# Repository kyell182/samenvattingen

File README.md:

# Samenvattingen ICT & Elektronica

Studiemateriaal uit mijn opleiding Elektronica-ICT aan VIVES: samenvattingen, cheatsheets, labo-verslagen en uitgewerkte opdrachten, geordend per jaar en per vak.

## Overzicht

### 1ste jaar

| Vak | Inhoud |
| :-- | :-- |
| [Digital technologie](1ste-jaar/digital%20technologie/) | Digitaal rekenen, logische poorten, tellers en flip-flops |
| [Electronica STEM](1ste-jaar/electronica%20stem/) | Weerstanden, dioden, versterkers en oscilloscoop |
| [Electronics](1ste-jaar/electronics/) | Theorie, LTspice-labo en examenvoorbereiding |
| [Introduction to gaming](1ste-jaar/introduction%20to%20gaming/) | Hardwareanalyse van de PlayStation 4 Pro |
| [Microsoft management](1ste-jaar/microsoft%20management/) | Netwerkbeheer met Windows Server 2022 |
| [PCB design](1ste-jaar/pcb%20design/) | Schema's en printplaten (LM555, IO-expander) |
| [Prototyping](1ste-jaar/prototyping/) | 3D-printen, lasersnijden en Arduino |
| [Web essentials](1ste-jaar/web%20essentials/) | HTML, CSS, Bootstrap, JavaScript en Web API's |

### 2de jaar

| Vak | Inhoud |
| :-- | :-- |
| [AI Fundamentals](2de-jaar/AI%20Fundamentals/) | Machine learning, neurale netwerken en zoekalgoritmen |
| [AI Programming](2de-jaar/AI%20Programming/) | Python, NumPy, pandas en PyTorch |
| [AI math](2de-jaar/ai%20math/) | Vectoren, matrices en de wiskunde achter AI |
| [Applied Math](2de-jaar/Applied%20Math/) | Lettervormen, vergelijkingen, afgeleiden en integralen |
| [Computer architectuur](2de-jaar/computer%20architectuur/) | Processoren, geheugen en prestatieverbetering |
| [Cybersecurity](2de-jaar/cybersecurity/) | Nmap, OSINT, Hashcat en picoCTF-challenges |
| [Databases](2de-jaar/Databases/) | Databankontwerp, SQL en security |
| [IoT devices](2de-jaar/IoT%20devices/) | I2C, SPI, WiFi en RTOS op microcontrollers |
| [Linux](2de-jaar/Linux/) | Systeembeheer, rechten, netwerk en containers |

### 3de jaar

Nog niet gestart.

## Structuur

```
samenvattingen/
  1ste-jaar/<vak>/     samenvattingen, cursusmateriaal, labo's en opdrachten
  2de-jaar/<vak>/
  3de-jaar/
  index.md             startpagina van de website
  _config.yml          Jekyll-instellingen
  .github/workflows/   automatische publicatie naar GitHub Pages
```

Elk vak heeft een `index.md` met een overzicht van de beschikbare bestanden. Samenvattingen zijn geschreven in markdown, bijbehorende bronbestanden zijn PDF, Word of Excel.

## Website lokaal bekijken

De repo wordt met Jekyll gepubliceerd op GitHub Pages. Om de site lokaal te testen heb je Ruby en Bundler nodig:

```bash
gem install jekyll bundler
jekyll serve
```

De site is daarna bereikbaar op `http://localhost:4000`.

## Gebruik

Het materiaal is bedoeld als persoonlijke studiehulp en kan fouten bevatten. Controleer belangrijke zaken altijd in de officiële cursus.

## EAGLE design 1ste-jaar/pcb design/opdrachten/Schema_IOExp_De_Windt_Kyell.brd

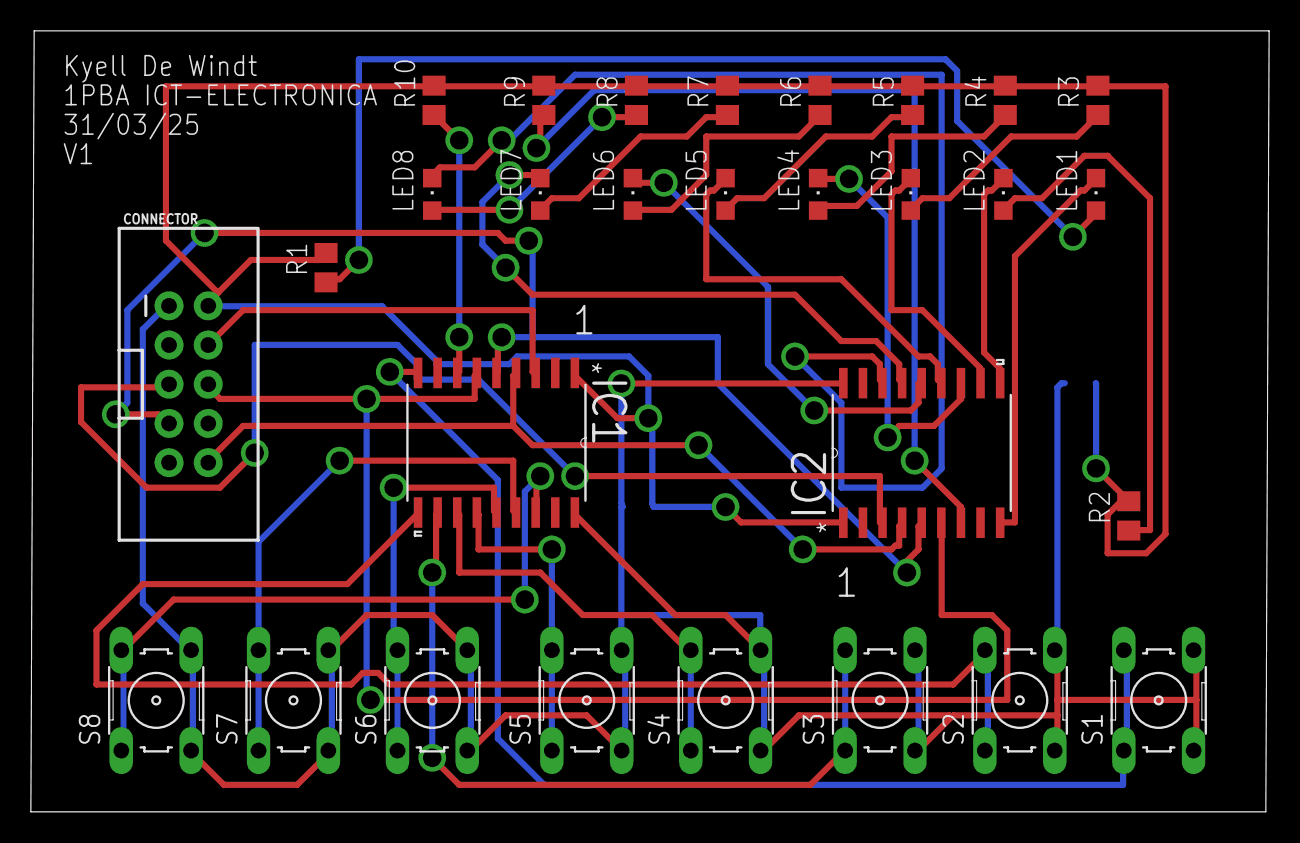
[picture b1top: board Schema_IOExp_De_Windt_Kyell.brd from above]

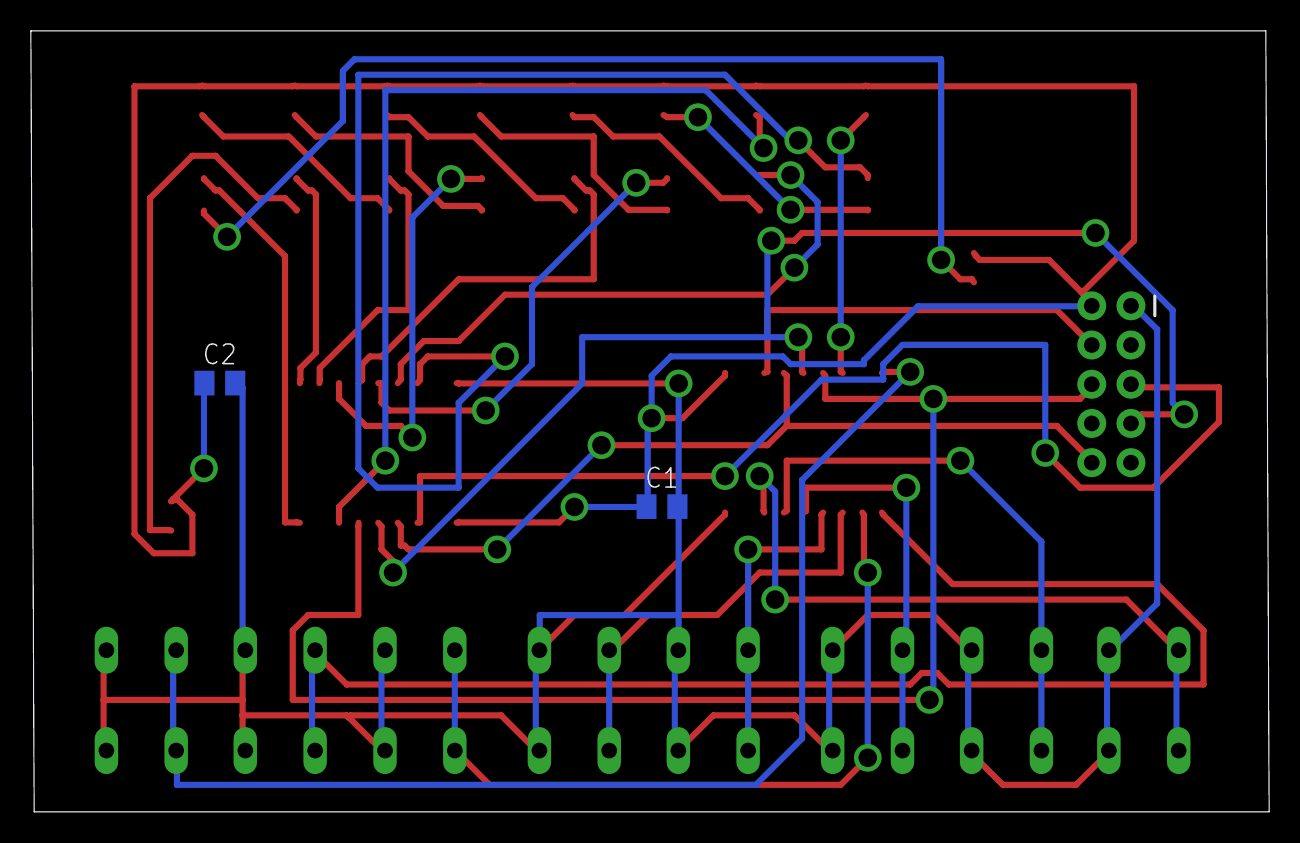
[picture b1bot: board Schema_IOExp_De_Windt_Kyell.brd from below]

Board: 2 copper layers, 80.2 x 50.6 mm, 31 parts (2 on the bottom side), 33 nets.

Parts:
C1, C2: 100nF; C0805K
CONNECTOR: SV1; 2X5-SHROUDED
IC1, IC2: MCP23S09-E/SO; SOIC127P1030X265-18N
LED1, LED2, LED3, LED4: groen; CHIPLED_0805
LED5, LED6: geel; CHIPLED_0805
LED7, LED8: rood; CHIPLED_0805
R1, R2: 10K; R0805
R3, R4, R5, R6, R7, R8: 100; R0805
R9, R10: 68; R0805
S1, S2, S3, S4, S5, S6, S7, S8: B3F-10XX

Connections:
CH1: CONNECTOR.4, IC1.3
CH2: CONNECTOR.5, IC2.3
DRUKKNOP1: IC1.9, S1.1, S1.2
DRUKKNOP2: IC1.10, S2.1, S2.2
DRUKKNOP3: IC1.11, S3.1, S3.2
DRUKKNOP4: IC1.12, S4.1, S4.2
DRUKKNOP5: IC1.13, S5.1, S5.2
DRUKKNOP6: IC1.14, S6.1, S6.2
DRUKKNOP7: IC1.15, S7.1, S7.2
DRUKKNOP8: IC1.16, S8.1, S8.2
GND: C1.2, C2.2, CONNECTOR.1, IC1.18, IC2.18, S1.3, S1.4, S2.3, S2.4, S3.3, S3.4, S4.3, S4.4, S5.3, S5.4, S6.3, S6.4, S7.3, S7.4, S8.3, S8.4
LED1: IC2.9, LED1.C
LED2: IC2.10, LED2.C
LED3: IC2.11, LED3.C
LED4: IC2.12, LED4.C
LED5: IC2.13, LED5.C
LED6: IC2.14, LED6.C
LED7: IC2.15, LED7.C
LED8: IC2.16, LED8.C
MISO: CONNECTOR.6, IC1.6, IC2.6
MOSI: CONNECTOR.7, IC1.5, IC2.5
unnamed: LED8.A, R8.1
unnamed: LED7.A, R7.1
unnamed: LED6.A, R6.1
unnamed: LED5.A, R5.1
unnamed: LED4.A, R4.1
unnamed: LED3.A, R3.1
unnamed: LED2.A, R2.1
unnamed: LED1.A, R1.1
unnamed: IC2.7, R9.1
unnamed: IC1.7, R10.1
SCK: CONNECTOR.10, IC1.4, IC2.4
VDD: C1.1, C2.1, CONNECTOR.2, IC1.1, IC2.1, R1.2, R2.2, R3.2, R4.2, R5.2, R6.2, R7.2, R8.2, R9.2, R10.2

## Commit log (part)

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2025-12-29 Fresh start - cleaned repository
2025-12-29 Remove nested submodules from tracking
2025-12-29 added readme quiz iot
2025-12-29 update iot readme
2025-12-29 Format answers as bullet points for clarity in IoT questions.
2025-12-29 Refactor IoT study guide: update structure and quiz questions for clarity and consistency
2025-12-30 Refactor code structure and remove redundant code blocks for improved readability and maintainability
2025-12-30 Fix formatting of question 3.1 for consistency in IoT devices README
2025-12-30 Improve formatting and clarity of polling, interrupt, and DMA sections in IoT devices README
2025-12-30 Fix bullet point formatting for clarity in advantages and disadvantages sections of IoT devices README
2025-12-30 Add chapters and assets for Databases course
    - Added Chapter 5: Calculated fields and functions (PDF)
    - Added Chapter 6: Joins (PDF)
    - Added Chapter 7: Subqueries (PDF)
    - Added Chapter 8: Write queries (PDF)
    - Added Chapter 9: Views, functions, and stored procedures (PDF)
    - Added various assets including images for data flow, Excel, CSV, and infographics
2025-12-30 Fix detail tag formatting to ensure proper rendering in Databases summary
2025-12-30 Refactor code structure for improved readability and maintainability
2025-12-30 Fix image file naming for XML and JSON file types for consistency
2025-12-30 Add additional file types and corresponding images to the Databases summary
2025-12-30 Improve formatting and clarity in DBMS section of Databases summary
2025-12-30 Fix formatting issue in RDBMS section for consistency
2025-12-30 Fix typos and improve clarity in database summary documentation
2025-12-30 Add new chapters on database design and SQL queries to the documentation
2025-12-30 Add ERD examples and symbols to the database summary documentation
2025-12-30 Add sample data insertion for 'leden' table in database documentation
2025-12-30 Remove unnecessary image for database creation example in documentation
2026-01-01 Add a newline before the chapter heading for better formatting
2026-01-01 Format SQL queries in code blocks for better readability
2026-01-01 Format SQL code in a code block for improved readability
2026-01-01 added ai fundamentals
2026-01-02 Format mathematical equations for improved clarity and consistency
2026-01-02 Add images for speed and acceleration calculations to enhance understanding
2026-01-02 Add images for speed and acceleration to enhance learning resources
2026-01-02 rrrr
2026-01-02 Fix calculation error in AI Fundamentals summary for clarity
2026-01-02 mind is exploding
2026-01-02 Enhance explanation of Perceptron as a linear classifier for clarity
2026-01-02 Add perceptron dataset image to AI Fundamentals summary
2026-01-02 Add introduction to Perceptron Learning Algorithm in AI Fundamentals summary
2026-01-02 Add techniques to improve convergence speed of Perceptron Learning Algorithm and include normalization image
2026-01-03 added ai math
2026-01-03 Add vector graphics for various mathematical concepts
    - Added 'nul vector grafisch.png' to represent the null vector visually.
    - Added 'nul vector.png' for a different representation of the null vector.
    - Introduced 'vecor in oorsprong grafisch.png' to illustrate the vector in its original form.
    - Included 'vector in de oorsprong .png' to depict the vector in its origin.
    - Added 'vector in de oorsprong .png' for additional visual representation of vectors in their origin.
2026-01-03 Fix notation for vector norm in AI math summary
2026-01-03 Fix formatting for unit vector notation in AI math summary
2026-01-03 Fix notation for vector addition in 3D representation
2026-01-03 Fix formatting issues in vector representation for clarity
2026-01-03 Fix formatting issues in 2D vector representation for consistency
2026-01-03 Add clarification on orthogonality of basis vectors in 2D representation
2026-01-03 Fix formatting issues in 2D basis vector representation for clarity
2026-01-03 Fix formatting issues in 2D basis vector representation for consistency
2026-01-03 Fix formatting issues in 3D basis vector representation for clarity
2026-01-03 Add clarification on scalar multiplication and distance between points in vector representation
2026-01-04 update linux folder with tagged pdfs and additional resources
2026-01-05 Add detailed descriptions for common Linux commands and enhance clarity
2026-01-05 Fix example of relative path in Linux guide for accuracy
2026-01-07 added computer architectuur
2026-01-08 Add 6502 microprocessor instruction set and reference questions
    - Introduced a comprehensive markdown document detailing the instruction set for the 6502 microprocessor, including various categories such as loading and storing registers, arithmetic operations, lo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
    - Added a reference document containing questions and answers related to computer architecture, covering topics from the history of computing to modern processor architectures and performance techniq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
2026-01-08 added h2
2026-01-08 fixed ascii garbage
2026-01-08 Add details on page directory and table entries for virtual memory explanation
2026-01-08 Update virtual memory explanation with additional details on page directory and table entries
2026-01-08 Fix indentation and formatting issues in virtual memory explanation
2026-01-09 h8 klaar
2026-01-09 h9 klaar
2026-01-15 Fix formatting issues in mathematical expressions and update flowchart structure for clarity
2026-01-15 Improve formatting and clarity of k-Nearest Neighbor algorithm section with additional details and mathematical expressions
2026-01-15 Update sigmoid function representation and clarify Hebb rule description
2026-01-17 Add comprehensive cheatsheets for Python libraries and AI programming concepts
    - Created a summary document for AI Programming covering key concepts and definitions.
    - Added cheatsheets for argparse, datetime, json, math, matplotlib, numpy, os, pandas, pytorch, queue, random, and requests libraries.
2026-01-17 Add alpha-beta pruning explanation and genetic algorithms overview
2026-01-17 Fix math formatting for alpha-beta pruning explanation
2026-01-18 Add advanced evolutionary approaches and swarm intelligence concepts
2026-01-18 Refine formatting of stop criteria for Ant Colony Optimization algorithm
2026-01-18 afgewerkte sammvating AI programming
2026-01-19 Update section title and clarify particle position update explanation in swarm intelligence
2026-01-19 Add section break before the ant optimization algorithm explanation
2026-01-19 Add explanation for the importance of fitness function in genetic algorithms
2026-01-19 Add explanation for chromosome encoding in genetic algorithms
2026-01-19 Update calculation for function f(e) to include additional path cost
2026-01-19 Refactor terminology section to improve clarity and formatting of graph-related terms
2026-01-19 Fix order of nodes in graph example for clarity
2026-01-19 Refactor tree terminology section for improved clarity and formatting
2026-01-19 DZDZD
2026-01-20 Add GitHub Actions workflow for static site deployment
    This workflow automates the deployment of static content to GitHub Pages upon pushes to the main branch or manually via the Actions tab.
2026-01-20 Add initial HTML structure for the website
2026-01-20 Remove obsolete subproject reference for oefenreeksen-kyell182
2026-01-20 adjustment voor web deploylment
2026-01-20 Add configuration file for site settings
2026-01-20 Remove index.html and add index.md for course site content
2026-01-20 update voor site
2026-01-20 Update submodules
2026-01-20 Add GitHub Actions workflow for Jekyll deployment
    This workflow builds and deploys a Jekyll site to GitHub Pages, including setup and artifact upload steps.
2026-01-20 Mark subproject commits as dirty for multiple microcontroller projects
2026-01-20 Remove subproject reference from programming directory
2026-01-20 hyhry
2026-01-20 reerror
2026-01-20 Add index.md files for Jekyll
2026-01-21 formularium
2026-02-09 Add comprehensive Nmap and cybersecurity notes
    - Introduced a new markdown file for Nmap notes covering its purpose and functionalities.
    - Detailed various types of cyberattacks, including passive and active attacks.
    - Explained the roles of red team and blue team in cybersecurity.
    - Defined different types of hackers: grey hat, white hat, and black hat.
    - Discussed defense methods and the three pillars of cybersecurity: Confidentiality, Integrity, and Availability.
    - Provided an overview of malware types and their components.
2026-02-09 Add cybersecurity killchain details and Nmap usage examples
2026-02-15 Add Nmap cheat sheet with common commands and usage explanations
2026-03-02 Add comprehensive notes on cryptography and its applications
2026-04-13 Add documentation for Metasploitable and network security concepts
    - Created a new markdown file for Metasploitable with various commands and tools used in cybersecurity, including nmap, netdiscover, and exploitation techniques.
    - Added a new markdown file for network security covering topics such as Shodan, NAT, CVE, DDoS attacks, DNS poisoning, and firewall functionalities.
2026-04-21 Add RDP configuration overview with detailed options and explanations
2026-05-16 added challenges cybersecurity
2026-05-18 Fix image path and improve formatting in Invisible words.md
2026-05-23 update van samenvattingen
2026-05-23 Refactor and enhance cybersecurity documentation: update Nmap notes, improve network security summary, and clarify attack vectors and defense strategies.
2026-05-23 Add OSINT and Wazuh practical guides for cybersecurity training
2026-05-23 Fix image path in Invisible words.md for correct asset reference

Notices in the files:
parts and their libraries:
SparkFun-Connectors: Licensing: Creative Commons ShareAlike 4.0 International - https://creativecommons.org/licenses/by-sa/4.0
